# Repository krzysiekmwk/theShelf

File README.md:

# theShelf

YouTube:
https://youtu.be/981hyT0ZYCw

Main button
1.	Click the button (everything is turn off) - set first menu - yellow lights
2.	Click the button when is turn on - turn off everything (don't save state to memory)

Menu:
1.	Yellow lights

	a.	Rotary encoder can change the light intensity
	
	b.	long press encoder button -> save actual light intensity
	
	c.	short press encoder button -> set menut state 2. 
	
2.	Colorful state

	a.	Rotary encoder can change the light colour. Colours are change like in rainbow.
	
	b.	long press encoder button -> save actual light colour
	
	c.	short press encoder button -> set menut state 3. 
	
3.	White lights

	a.	Rotary encoder can change the light intensity
	
	b.	long press encoder button -> save actual light intensity
	
	c.	short press encoder button -> set menut state 1.

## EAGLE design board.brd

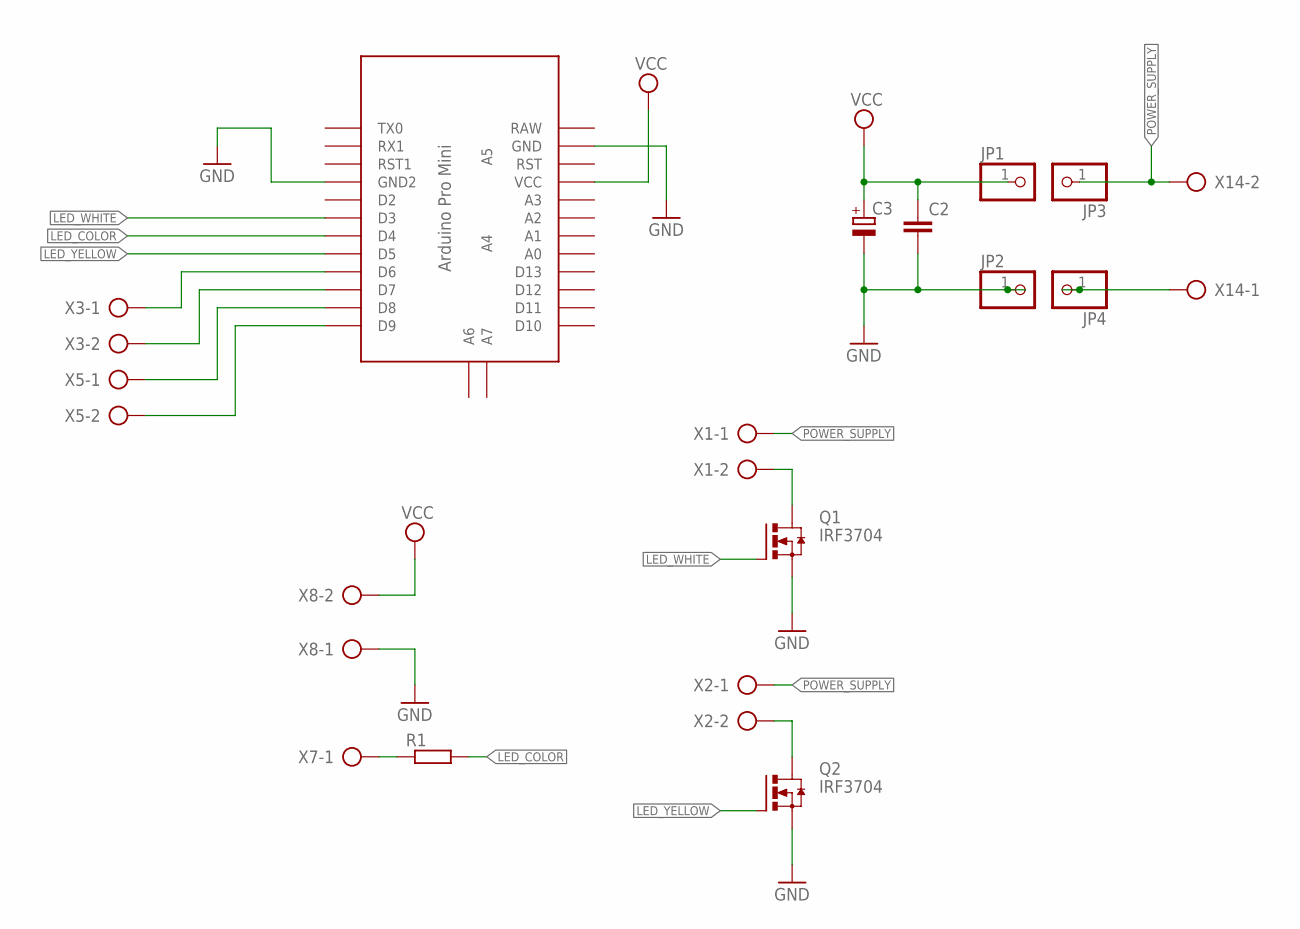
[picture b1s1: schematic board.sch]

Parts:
C2: C-EU050-025X075; C050-025X075
C3: CPOL-EUE3.5-8; E3,5-8
JP1, JP2, JP3, JP4: PINHD-1X1; 1X01
Q1, Q2: IRF3704; TO220AH
R1: R-EU_0204/7; 0204/7
U$1: ABK-PRO-MINI
X1, X2, X3, X5, X7, X8, X14: AK500/2-H

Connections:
GND: C2.2, C3.-, JP2.1, JP4.1, Q1.E (S), Q2.E (S), U$1.GND, U$1.GND1 (GND2), X8.1, X14.1
LED_COLOR: R1.2, U$1.D4
LED_WHITE: Q1.B (G), U$1.D3
LED_YELLOW: Q2.B (G), U$1.D5
unnamed: U$1.D9, X5.2
unnamed: Q1.C (D), X1.2
unnamed: Q2.C (D), X2.2
unnamed: R1.1, X7.1
unnamed: U$1.D6, X3.1
unnamed: U$1.D7, X3.2
unnamed: U$1.D8, X5.1
POWER_SUPPLY: JP3.1, X1.1, X2.1, X14.2
VCC: C2.1, C3.+, JP1.1, U$1.VCC, X8.2

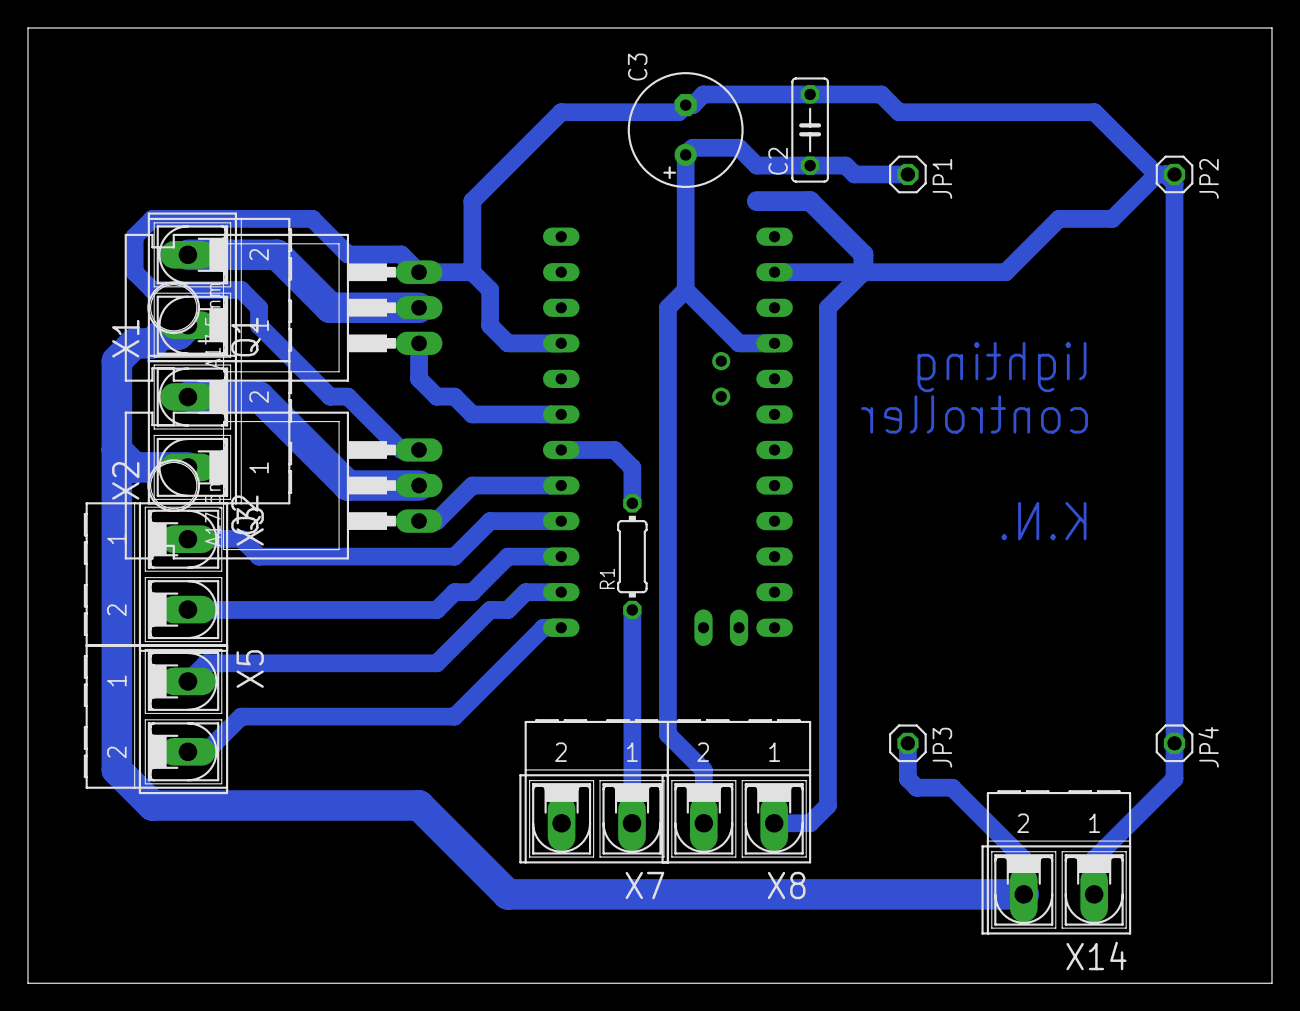
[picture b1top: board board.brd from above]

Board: 2 copper layers, 88.9 x 68.2 mm, 17 parts (0 on the bottom side), 13 nets.

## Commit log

2018-03-31 arduino code
2018-03-31 comments in English
2018-03-31 how program works - description
2018-03-31 Eagle files for arduino pro mini
2018-03-31 board schematic
